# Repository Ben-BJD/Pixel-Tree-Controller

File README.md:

<div align="center">

# 🎄 PixelTree Node: High-Current ESP32 WLED Controller

---

**A robust, logic-shifted, and fused Power Distribution Hub for driving massive addressable LED arrays (up to 22A) with an ESP32-S3 and WLED.**

</div>

---

## 📖 Overview

Driving 800 WS2811 pixels at full brightness draws upwards of 16 Amps (192 Watts). Attempting to route this through breadboards, thin jumper wires, or standard microcontrollers results in melted plastic, ground loops, erratic flickering, and potential fire hazards. Furthermore, the ESP32 outputs a 3.3V logic signal, while WS2811 pixels strictly require 5V, leading to degraded data packets over long wire runs.

The **PixelTree Node v1.0** solves this. It is a custom-engineered PCB that acts as a safe, isolated, high-current brain for outdoor holiday light shows. It takes a massive 12V payload, distributes it safely across 8 automotive-fused branches, steps down power for an onboard ESP32-S3, and flawlessly level-shifts 8 data channels to 5V.

---

## 📸 Hardware Gallery

<div align="center">
 
| Assembled Board | 3D Render |
| :---: | :---: |
|  |  |

| PCB Front | PCB Back |
| :---: | :---: |
|  |  |

<details>
<summary><b>Click to view Schematic</b></summary>
<br>

</details>

</div>

---

## ✨ Key Features

*   **Massive Power Handling**: Designed with heavy copper polygon pours and 3.0mm output traces. Safely distributes up to 22A of 12V DC power.
*   **Flawless Logic Shifting**: Utilizes an onboard `SN74HCT245` chip to cleanly shift the ESP32's 3.3V data signals up to a punchy 5V, ensuring zero data degradation over long pigtails.
*   **Integrated Voltage Step-Down**: An onboard `K7805` highly-efficient buck converter drops 12V down to a stable 5V for the microcontroller and logic chip, eliminating the need for dual power supplies.
*   **Independent Automotive Fusing**: 8 individual output channels are protected by standard Mini Blade Fuses (e.g., 5A). If a wire shorts outdoors, the 50-cent fuse pops, protecting your display.
*   **Common Ground Architecture**: Front and back solid copper ground planes provide a rock-solid electrical reference point, completely eliminating erratic LED flickering caused by ground loops.
*   **Plug-and-Play WLED Integration**: Designed specifically around the ESP32-S3 footprint with 8 dedicated hardware output pins perfectly suited for WLED's 2D Matrix capabilities.

---

## 🏗️ Architecture & Tech Stack

| Component / Tool | Details |
| :--- | :--- |
| **EDA Software** | KiCad (Designed using standard 1.6mm FR4 / 1oz Copper limits) |
| **Microcontroller** | `ESP32-S3-DevKitC-1U-N8R8` (Wi-Fi, Dual Core, RMT Peripheral for LEDs) |
| **Logic Shifter** | `SN74HCT245PWR` (8-Channel Octal Bus Transceiver) |
| **Buck Converter** | `K7805-1000R3` (12V in, 5V out, High Efficiency) |
| **Terminals** | `HB9500-9.5-2P` (Main Input) & `KF2EDGR-5.08-3P` (xConnect Pigtail Outputs) |
| **Firmware** | WLED (Web UI, E1.31 / DDP support, Pixel Art Matrix support) |

---

## 🚀 Quick Start & Manufacturing

### 1. Fabricating the Board
This project relies on high-current traces and surface-mount (SMD) components. We highly recommend utilizing a turnkey assembly service.

1. Download the [Latest Release Zip](Pixel-Tree-Controller.kicad_pcb.zip).

### 2. Software Installation (WLED)
1. Plug your `ESP32-S3` into your computer via USB.
2. Navigate to [install.wled.me](https://install.wled.me/) using a Web Serial compatible browser (Chrome/Edge).
3. Flash the latest stable release and configure your Wi-Fi credentials.
4. Insert the ESP32 into the completed PCB (ensure the board is **powered off** before inserting the microcontroller).

---

## ⚙️ WLED Configuration & Pin Mapping

This board relies on **Serpentine Wiring (Folding)**. Each of the 8 ports drives two 50-pixel strings connected end-to-end (100 pixels per port). Because we use 12V WS2811 pixels, the voltage drop is minimal, and power injection at the 100th pixel is not required.

### Output Port Mapping

| PCB Port | ESP32 GPIO | Pixels Driven | WLED Matrix Role |
| :---: | :---: | :---: | :--- |
| **CN1** | `GPIO 4` | 0 - 99 | Strands 1 (UP) & 2 (DOWN) |
| **CN2** | `GPIO 5` | 100 - 199 | Strands 3 (UP) & 4 (DOWN) |
| **CN3** | `GPIO 6` | 200 - 299 | Strands 5 (UP) & 6 (DOWN) |
| **CN4** | `GPIO 7` | 300 - 399 | Strands 7 (UP) & 8 (DOWN) |
| **CN5** | `GPIO 8` | 400 - 499 | Strands 9 (UP) & 10 (DOWN) |
| **CN6** | `GPIO 9` | 500 - 599 | Strands 11 (UP) & 12 (DOWN) |
| **CN7** | `GPIO 10` | 600 - 699 | Strands 13 (UP) & 14 (DOWN) |
| **CN8** | `GPIO 11` | 700 - 799 | Strands 15 (UP) & 16 (DOWN) |

---

## ⚠️ Safety Warnings & "The Multimeter Trap"

> **IMPORTANT:** When probing this newly assembled board for shorts using a cheap multimeter in "Continuity" mode, it may beep continuously between 12V and GND. **Do not panic.** Cheap multimeters beep for anything under 1,000 Ohms.
>
> If you switch to **Resistance (Ohms)** mode, you will likely read ~600 Ω from 12V to GND. This is a 20mA draw—merely the resting resistance of the `K7805` buck converter. A true dead short (solder bridge) will read between 0 Ω and 1.5 Ω.

*   **Always apply 12V power *without* the ESP32 inserted first.** Probe the 5V socket pins to ensure the buck converter is functioning correctly. If it has failed and is passing 12V, it will instantly destroy your ESP32.
*   **Never insert or remove the ESP32 while the board is powered.**
*   Always use appropriately rated automotive fuses (e.g., 5A) for each channel to protect against outdoor shorts.

---

## 🤝 Contributing

Contributions, issues, and feature requests are welcome!

If you want to contribute to the KiCad schematic or routing:
1. Fork the Project.
2. Create your Feature Branch (`git checkout -b feature/AmazingFeature`).
3. Commit your Changes (`git commit -m 'Add some AmazingFeature'`).
4. Push to the Branch (`git push origin feature/AmazingFeature`).
5. Open a Pull Request.

---

## 📝 License

Distributed under the CERN Open Hardware License Version 2 - Permissive.

> Designed by **BJD Solutions**

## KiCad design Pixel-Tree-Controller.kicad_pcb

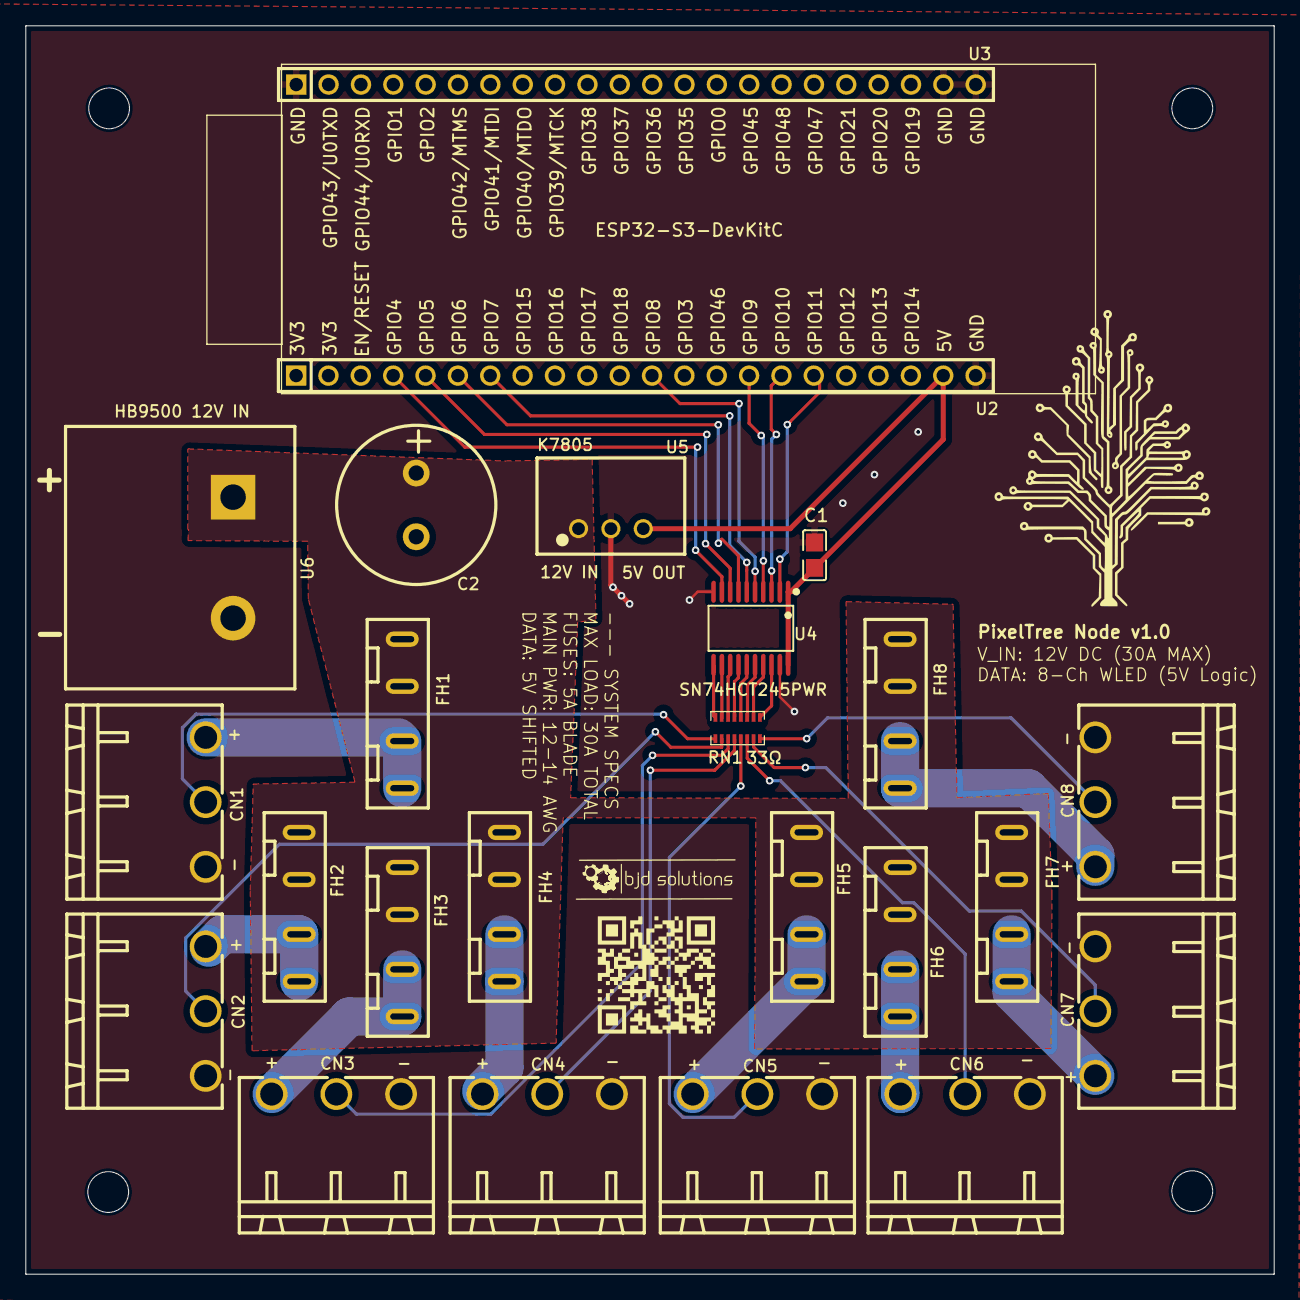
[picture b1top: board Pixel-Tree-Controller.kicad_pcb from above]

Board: 2 copper layers, 98.0 x 98.0 mm, 28 parts (0 on the bottom side), 35 nets.

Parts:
C1: 0.1uf; C0805
C2: 1000uF; CAP-TH_BD12.5-P5.00-D0.6-FD
CN1, CN2, CN3, CN4, CN5, CN6, CN7, CN8: KF2EDGR-5.08-3P; CONN-TH_3P-P5.08_KF2EDGR-5.08-3P
FH1, FH2, FH3, FH4, FH5, FH6, FH7, FH8: XF-506P; FUSE-TH_XF-506P
H1, H2, H3, H4: MountingHole; MountingHole_3.2mm_M3
RN1: 33Ω; RES-ARRAY-SMD_16P-L3.8-W1.6-P0.50-BL
U2, U3: ZX-PM2.54-1-22PY; HDR-TH_22P-P2.54-V-F
U4: SN74HCT245PWR; TSSOP-20_L6.5-W4.4-P0.65-LS6.4-BL
U5: K7805; PWRM-TH_YLPTEC_K78XX-1000R3
U6: HB9500 12V IN; CONN-TH_HB9500-9.5-2P

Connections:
+5V: C1.1, U2.21, U4.1 (DIR), U4.20 (VCC), U5.3 (+VO)
+12V: C2.1, FH1.1, FH2.1, FH3.1, FH4.1, FH5.1, FH6.1, FH7.1, FH8.1, U5.1 (VIN), U6.1
GND: C1.2, C2.2, CN1.3, CN2.3, CN3.3, CN4.3, CN5.3, CN6.3, CN7.3, CN8.3, U2.22, U3.1, U3.21, U3.22, U4.10 (GND), U4.19 (#OE), U5.2 (GND), U6.2
GPIO4: U2.4, U4.9 (A8)
GPIO5: U2.5, U4.8 (A7)
GPIO6: U2.6, U4.7 (A6)
GPIO7: U2.7, U4.6 (A5)
GPIO8: U2.12, U4.5 (A4)
GPIO9: U2.15, U4.4 (A3)
GPIO10: U2.16, U4.3 (A2)
GPIO11: U2.17, U4.2 (A1)
unnamed: CN1.1, FH1.2
unnamed: CN2.1, FH2.2
unnamed: CN3.1, FH3.2
unnamed: CN4.1, FH4.2
unnamed: CN5.1, FH5.2
unnamed: CN6.1, FH6.2
unnamed: CN7.1, FH7.2
unnamed: CN8.1, FH8.2
unnamed: RN1.1, U4.18 (B1)
unnamed: RN1.2, U4.17 (B2)
unnamed: RN1.3, U4.16 (B3)
unnamed: RN1.4, U4.15 (B4)
unnamed: RN1.5, U4.14 (B5)
unnamed: RN1.6, U4.13 (B6)
unnamed: RN1.7, U4.12 (B7)
unnamed: RN1.8, U4.11 (B8)
PXL_DAT_01: CN1.2, RN1.9
PXL_DAT_02: CN2.2, RN1.10
PXL_DAT_03: CN3.2, RN1.11
PXL_DAT_04: CN4.2, RN1.12
PXL_DAT_05: CN5.2, RN1.13
PXL_DAT_06: CN6.2, RN1.14
PXL_DAT_07: CN7.2, RN1.15
PXL_DAT_08: CN8.2, RN1.16
